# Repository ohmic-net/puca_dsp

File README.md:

# PÚCA DSP

**PÚCA DSP** is an open source, Arduino compatible ESP32 development board for audio and digital signal processing applications. In this repository you will find the hardware design files, and software examples for; 
- Arduino IDE
- VSCode/PlatformIO with Platform Espressif 32 and Framework arduinoespressif32 
- VSCode/PlatformIO with Platform Espressif 32 and Framework espidf
- ESP IDF

# Specifications 

**Processor & Memory**
- Espressif ESP32 Pico D4 Processor
- 32-bit dual core 80MHZ / 160MHZ / 240MHZ
- 4MB SPI Flash with 8MB additional PSRAM or 16MB External SPI Flash 
- Wireless 2.4GHz Wi-Fi -802.11b/g/n
- Bluetooth BLE 4.2
- 3D Antenna

**Audio**
- Wolfson WM8978 Stereo Audio Codec
- Audio Line In on stereo 3.5mm connector
- Audio Headphone / Line Out on stereo 3.5mm connector
- Stereo Aux Line In, Audio Mono Out routed to GPIO Header
- 2 x Knowles SPM0687LR5H-1 MEMS Microphones 
- ESD protection on all audio inputs and outputs
- Support for 8, 11.025, 12, 16, 22.05, 24, 32, 44.1 and 48kHz sample rates
- 1W Speaker Driver, routed to GPIO Header
- DAC SNR 98 dB, THD -84 dB (‘A’ weighted @ 48 kHz)
- ADC SNR 95 dB, THD -84 dB (‘A’ weighted @ 48 kHz)
- Line input impedance: 1 M ohm
- Line output impedance: 33 ohm

**Form Factor and Connectivity**
- Breadboard friendly
- 70mm x 24mm
- 11 x GPIO pins broken out to 2.54mm pitch header, with access to both ESP32 ADC channels, JTAG and capacitive touch pins
- USB 2.0 over USB Type C connector

**Power**
- 3.7/4.2v Lithium Polymer Rechargeable Battery, USB  or external 5V DC power source
- ESP32 and Audio Codec can be placed into low power modes under software control
- Battery voltage level detection
- ESD protection on USB data bus

# Documentation 

# Pin Description

# Absolute Maximum Ratings 

Maximum voltage before clipping on Audio Input, Aux L & Aux R = 3.3V peak-to-peak, AC. Audio input paths are AC coupled. 

Maximum voltage on GPIO pins = 3.3V DC. GPIO pins are not overvoltage protected, for voltages higher than 3.3V use an input protection circuit such as a diode clamp or a level shifter.

# Current Consumption Characteristics 

# Battery Voltage Monitoring
Battery voltage monitoring is available by soldering the BT_LVL solder jumper on the PCB top side, which routes the battery voltage to GPIO 14. 

# Physical Dimensions

*Height measurement is with pin headers soldered. 

# Open Source Licensing 

**PÚCA DSP** is Open Source Hardware Association certified, and can be found on the OSHWA website here; https://certification.oshwa.org/list.html

Hardware design files are released as open source under the CERN v1.2 license. **PÚCA DSP** software examples are released under the MIT license, software examples using Faust DSP also contain additional license information relevant to Faust DSP. Please review these licenses before using these files in your own projects to understand your obligations.

# Video Tutorials
1. Getting started with VS Code and PlatformIO IDE - https://www.youtube.com/watch?v=hKllKXUncVo
2. Configuring the audio codec - https://www.youtube.com/watch?v=Auh9VE7Pjl8

# Need a board?
There are a few available on Tindie - https://www.tindie.com/products/ohmic/puca-dsp/

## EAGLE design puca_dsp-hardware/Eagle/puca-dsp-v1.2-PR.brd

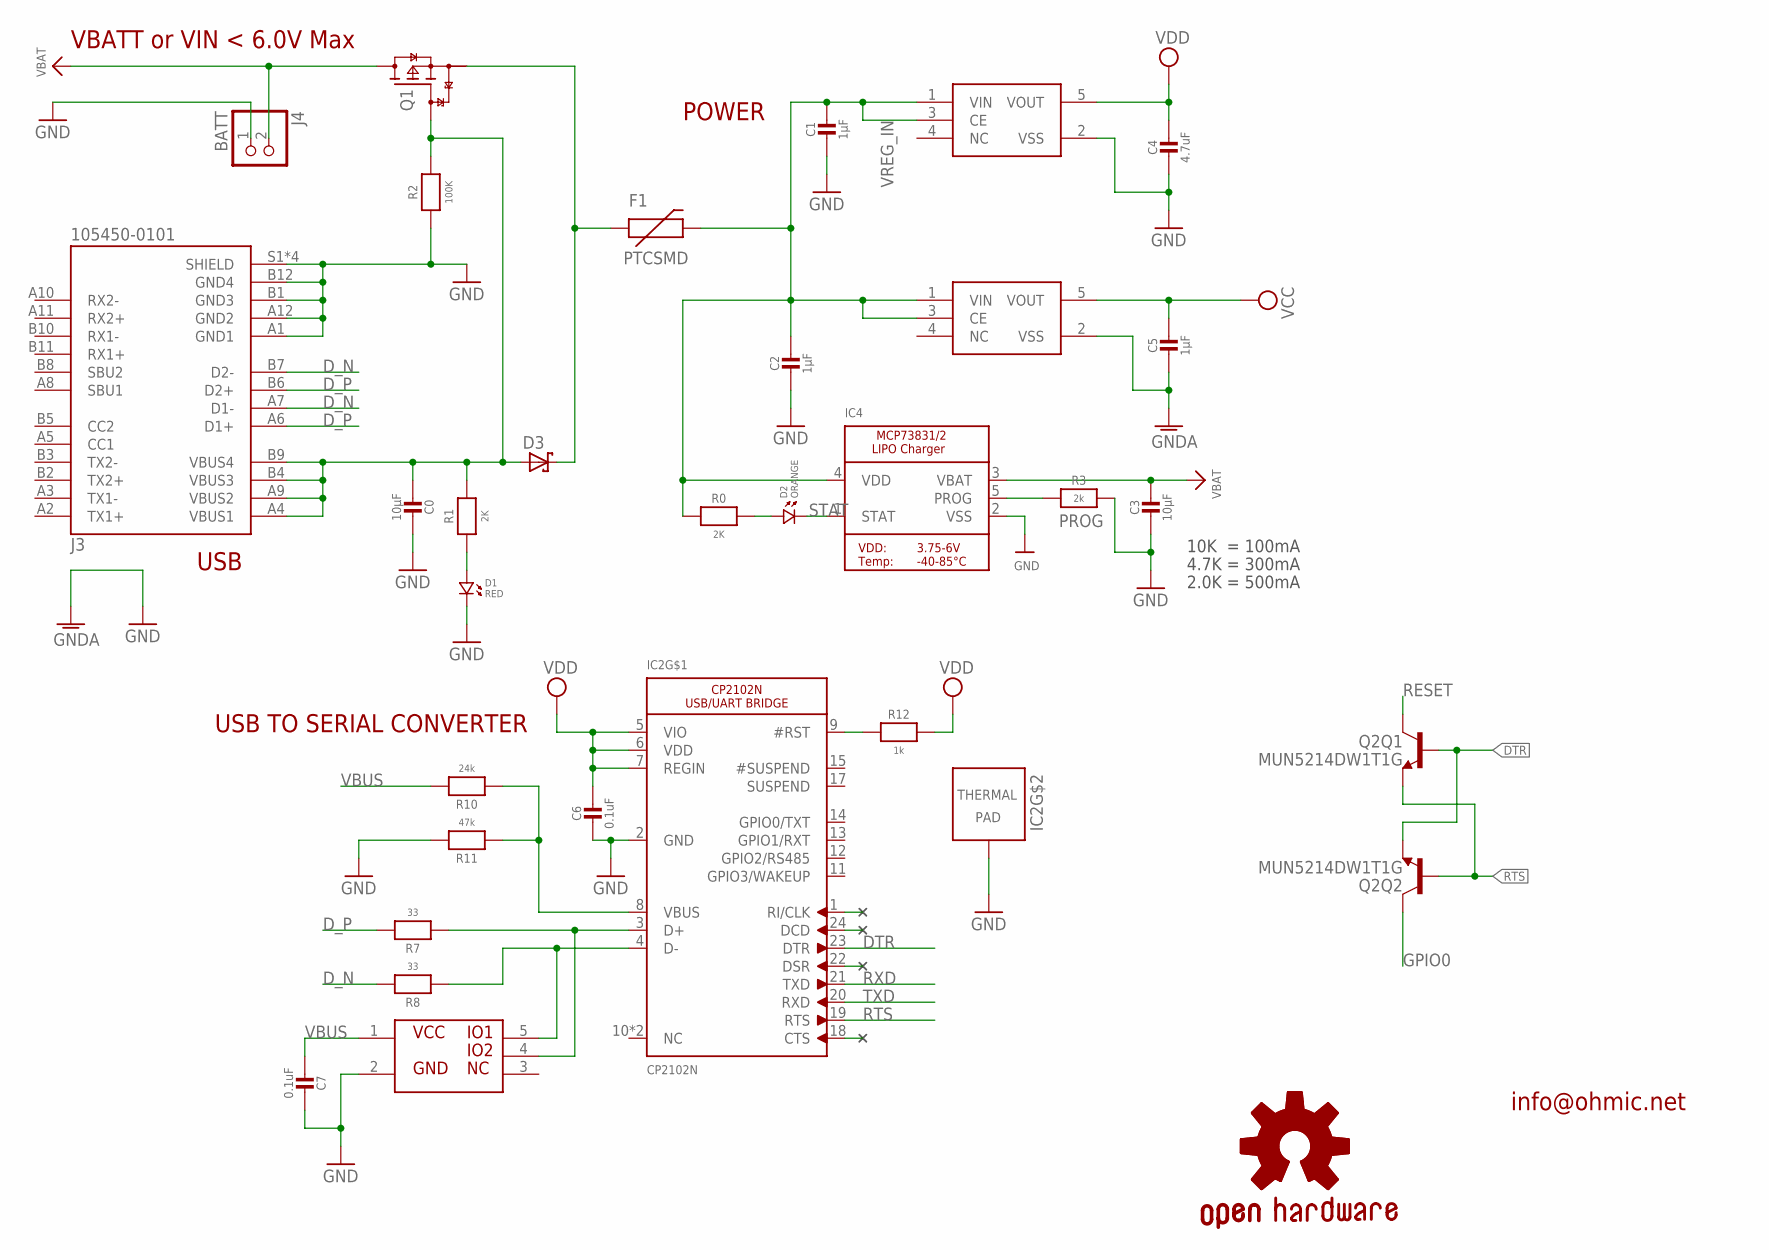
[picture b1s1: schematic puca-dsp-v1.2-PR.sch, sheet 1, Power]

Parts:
C0, C3: 10µF; _0603MP
C1, C2, C5: 1µF; _0402MP
C4: 4.7uF; _0402MP
C6, C7: 0.1uF; _0402MP
D1: RED; 0402.LED
D2: ORANGE; 0402.LED
D3: BAT60J; SOD323_ST
F1: PTCSMD; PTC-1206
GOLD_ORB_SM1: OSHWLOGO_GOLD_ORB_SM; OSHW2
IC2: CP2102N; MICROBUILDER_QFN24_4MM_SMSC
IC4: TP4065-4.2V-SOT25-R; SOT23-5
IC5, IC6: XC6210; SOT95P285X145-5N
IC8: NUP2114UPXV5T1G; SOT50P160X60-5N
J3: 105450-0101; MOLEX_105450-0101
J4: BATT; JST-PH-2-THM
Q1: SSM3J56ACT; SOT883(B)
Q2: MUN5214DW1T1G; DUAL_NPN_SC70-6
R0, R1: 2K; _0402MP
R2: 100K; _0402MP
R3: 2k; _0402MP
R7, R8: 33; _0402MP
R10: 24k; _0402MP
R11: 47k; _0402MP
R12: 1k; _0402MP

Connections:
D1_N: IC2.4 (D-), IC8.5, R8.1
D1_P: IC2.3 (D+), IC8.4, R7.1
DTR: IC2.23 (DTR), Q2.1 (E), Q2.5 (B)
D_N: J3.A7 (D1-), J3.B7 (D2-), R8.2
D_P: J3.A6 (D1+), J3.B6 (D2+), R7.2
GND: C0.1, C1.2, C2.2, C3.2, C4.2, C6.2, C7.1, D1.P$2 (2), IC2.2 (GND), IC2.THERM (TP), IC4.2 (VSS), IC5.2 (VSS), IC8.2, J3.A1 (GND1), J3.A12 (GND2), J3.B1 (GND3), J3.B12 (GND4), J3.S1 (SHIELD), J3.S2 (SHIELD), J3.S3 (SHIELD), J3.S4 (SHIELD), J4.1, R2.2, R3.2, R11.2; also elsewhere on the board
GNDA: C5.2, IC6.2 (VSS); also elsewhere on the board
GPIO0: Q2.6 (C); also elsewhere on the board
unnamed: D1.P$1 (1), R1.1
unnamed: D2.P$1 (1), R0.2
unnamed: IC2.8 (VBUS), R10.1, R11.1
unnamed: D3.C, F1.1, Q1.2 (S)
unnamed: IC2.9 (#RST), R12.1
PROG: IC4.5 (PROG), R3.1
RESET: Q2.3 (C); also elsewhere on the board
RTS: IC2.19 (RTS), Q2.2 (B), Q2.4 (E)
RXD: IC2.21 (TXD); also elsewhere on the board
STAT: D2.P$2 (2), IC4.1 (STAT)
TXD: IC2.20 (RXD); also elsewhere on the board
VBAT: C3.1, IC4.3 (VBAT), J4.2, Q1.3 (D); also elsewhere on the board
VBUS: C0.2, C7.2, D3.A, IC8.1, J3.A4 (VBUS1), J3.A9 (VBUS2), J3.B4 (VBUS3), J3.B9 (VBUS4), Q1.1 (G), R1.2, R2.1, R10.2
VCC: C5.1, IC6.5 (VOUT); also elsewhere on the board
VDD: C4.1, C6.1, IC2.5 (VIO), IC2.6 (VDD), IC2.7 (REGIN), IC5.5 (VOUT), R12.2; also elsewhere on the board
VREG_IN: C1.1, C2.1, F1.2, IC4.4 (VDD), IC5.1 (VIN), IC5.3 (CE), IC6.1 (VIN), IC6.3 (CE), R0.1

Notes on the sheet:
USB TO SERIAL CONVERTER
10K = 100mA
4.7K = 300mA
2.0K = 500mA
VBATT or VIN < 6.0V Max
POWER
info@ohmic.net
USB

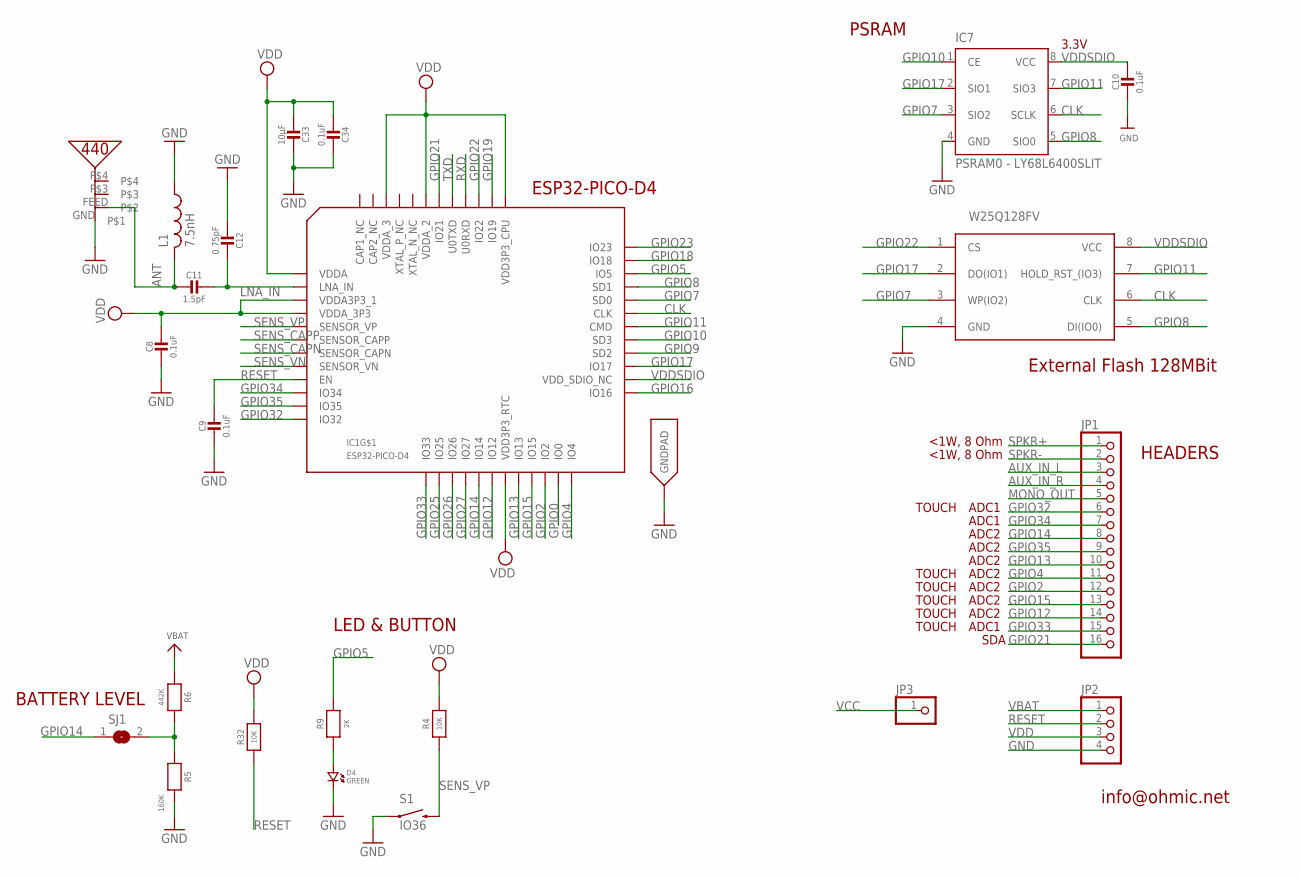
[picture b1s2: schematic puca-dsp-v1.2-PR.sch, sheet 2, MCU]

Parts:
C8, C9, C10, C34: 0.1uF; _0402MP
C11: 1.5pF; _0402MP
C12: 0.75pF; _0402MP
C33: 10µF; _0603MP
D4: GREEN; 0402.LED
IC1: ESP32-PICO-D4; PICO-D4-QFN48
IC7: PSRAM0 - LY68L6400SLIT; SOP8
IC12: PRO-OB-440
JP1: HEADER-1X16ROUND; 1X16_ROUND
JP2: HEADER-1X4ROUND; 1X04_ROUND
JP3: HEADER-1X1ROUND; 1X01_ROUND
L1: 7.5nH; RESC0402_N
R4, R32: 10K; _0402MP
R5: 160K; _0402MP
R6: 442K; _0402MP
R9: 2K; _0402MP
S1: IO36; TACTILE_SWITCH_SMD_4.6X2.8MM
SJ1: SOLDERJUMPER; SOLDERJUMPER_ARROW_NOPASTE
U$1: W25Q128FV; SOIC127P790X216-8N

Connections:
ANT: C11.2, IC12.FEED, L1.2
AUX_IN_L: JP1.3; also elsewhere on the board
AUX_IN_R: JP1.4; also elsewhere on the board
CLK: IC1.31 (CLK), IC7.6 (SCLK), U$1.6 (CLK)
GND: C8.2, C9.2, C10.2, C12.2, C33.1, C34.1, D4.P$2 (2), IC1.EXP (GNDPAD), IC7.4 (GND), IC12.GND, JP2.4, L1.1, R5.2, S1.1, S1.2 (1), U$1.4 (GND); also elsewhere on the board
GPIO0: IC1.23 (IO0); also elsewhere on the board
GPIO2: IC1.22 (IO2), JP1.12
GPIO4: IC1.24 (IO4), JP1.11
GPIO5: IC1.34 (IO5), R9.2
GPIO7: IC1.32 (SD0), IC7.3 (SIO2), U$1.3 (WP(IO2))
GPIO8: IC1.33 (SD1), IC7.5 (SIO0), U$1.5 (DI(IO0))
GPIO9: IC1.28 (SD2)
GPIO10: IC1.29 (SD3), IC7.1 (CE)
GPIO11: IC1.30 (CMD), IC7.7 (SIO3), U$1.7 (HOLD_RST_(IO3))
GPIO12: IC1.18 (IO12), JP1.14
GPIO13: IC1.20 (IO13), JP1.10
GPIO14: IC1.17 (IO14), JP1.8, SJ1.1
GPIO15: IC1.21 (IO15), JP1.13
GPIO16: IC1.25 (IO16)
GPIO17: IC1.27 (IO17), IC7.2 (SIO1), U$1.2 (DO(IO1))
GPIO18: IC1.35 (IO18); also elsewhere on the board
GPIO19: IC1.38 (IO19); also elsewhere on the board
GPIO21: IC1.42 (IO21), JP1.16
GPIO22: IC1.39 (IO22), U$1.1 (CS)
GPIO23: IC1.36 (IO23); also elsewhere on the board
GPIO25: IC1.14 (IO25); also elsewhere on the board
GPIO26: IC1.15 (IO26); also elsewhere on the board
GPIO27: IC1.16 (IO27); also elsewhere on the board
GPIO32: IC1.12 (IO32), JP1.6
GPIO33: IC1.13 (IO33), JP1.15
GPIO34: IC1.10 (IO34), JP1.7
GPIO35: IC1.11 (IO35), JP1.9
LNA_IN: C11.1, C12.1, IC1.2 (LNA_IN)
MONO_OUT: JP1.5; also elsewhere on the board
unnamed: R5.1, R6.2, SJ1.2
unnamed: D4.P$1 (1), R9.1
RESET: C9.1, IC1.9 (EN), JP2.2, R32.1; also elsewhere on the board
RXD: IC1.40 (U0RXD); also elsewhere on the board
SENS_CAPN: IC1.7 (SENSOR_CAPN)
SENS_CAPP: IC1.6 (SENSOR_CAPP)
SENS_VN: IC1.8 (SENSOR_VN)
SENS_VP: IC1.5 (SENSOR_VP), R4.1, S1.3 (2), S1.4 (2)
SPKR+: JP1.1; also elsewhere on the board
SPKR-: JP1.2; also elsewhere on the board
TXD: IC1.41 (U0TXD); also elsewhere on the board
VBAT: JP2.1, R6.1; also elsewhere on the board
VCC: JP3.1; also elsewhere on the board
VDD: C8.1, C33.2, C34.2, IC1.1 (VDDA), IC1.3 (VDDA3P3_1), IC1.4 (VDDA_3P3), IC1.19 (VDD3P3_RTC), IC1.37 (VDD3P3_CPU), IC1.43 (VDDA_2), IC1.46 (VDDA_3), JP2.3, R4.2, R32.2; also elsewhere on the board
VDDSDIO: C10.1, IC1.26 (VDD_SDIO_NC), IC7.8 (VCC), U$1.8 (VCC)

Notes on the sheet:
ESP32-PICO-D4
PSRAM
3.3V
External Flash 128MBit
LED & BUTTON
HEADERS
ADC1
<1W, 8 Ohm
ADC2
SDA
TOUCH
info@ohmic.net
BATTERY LEVEL

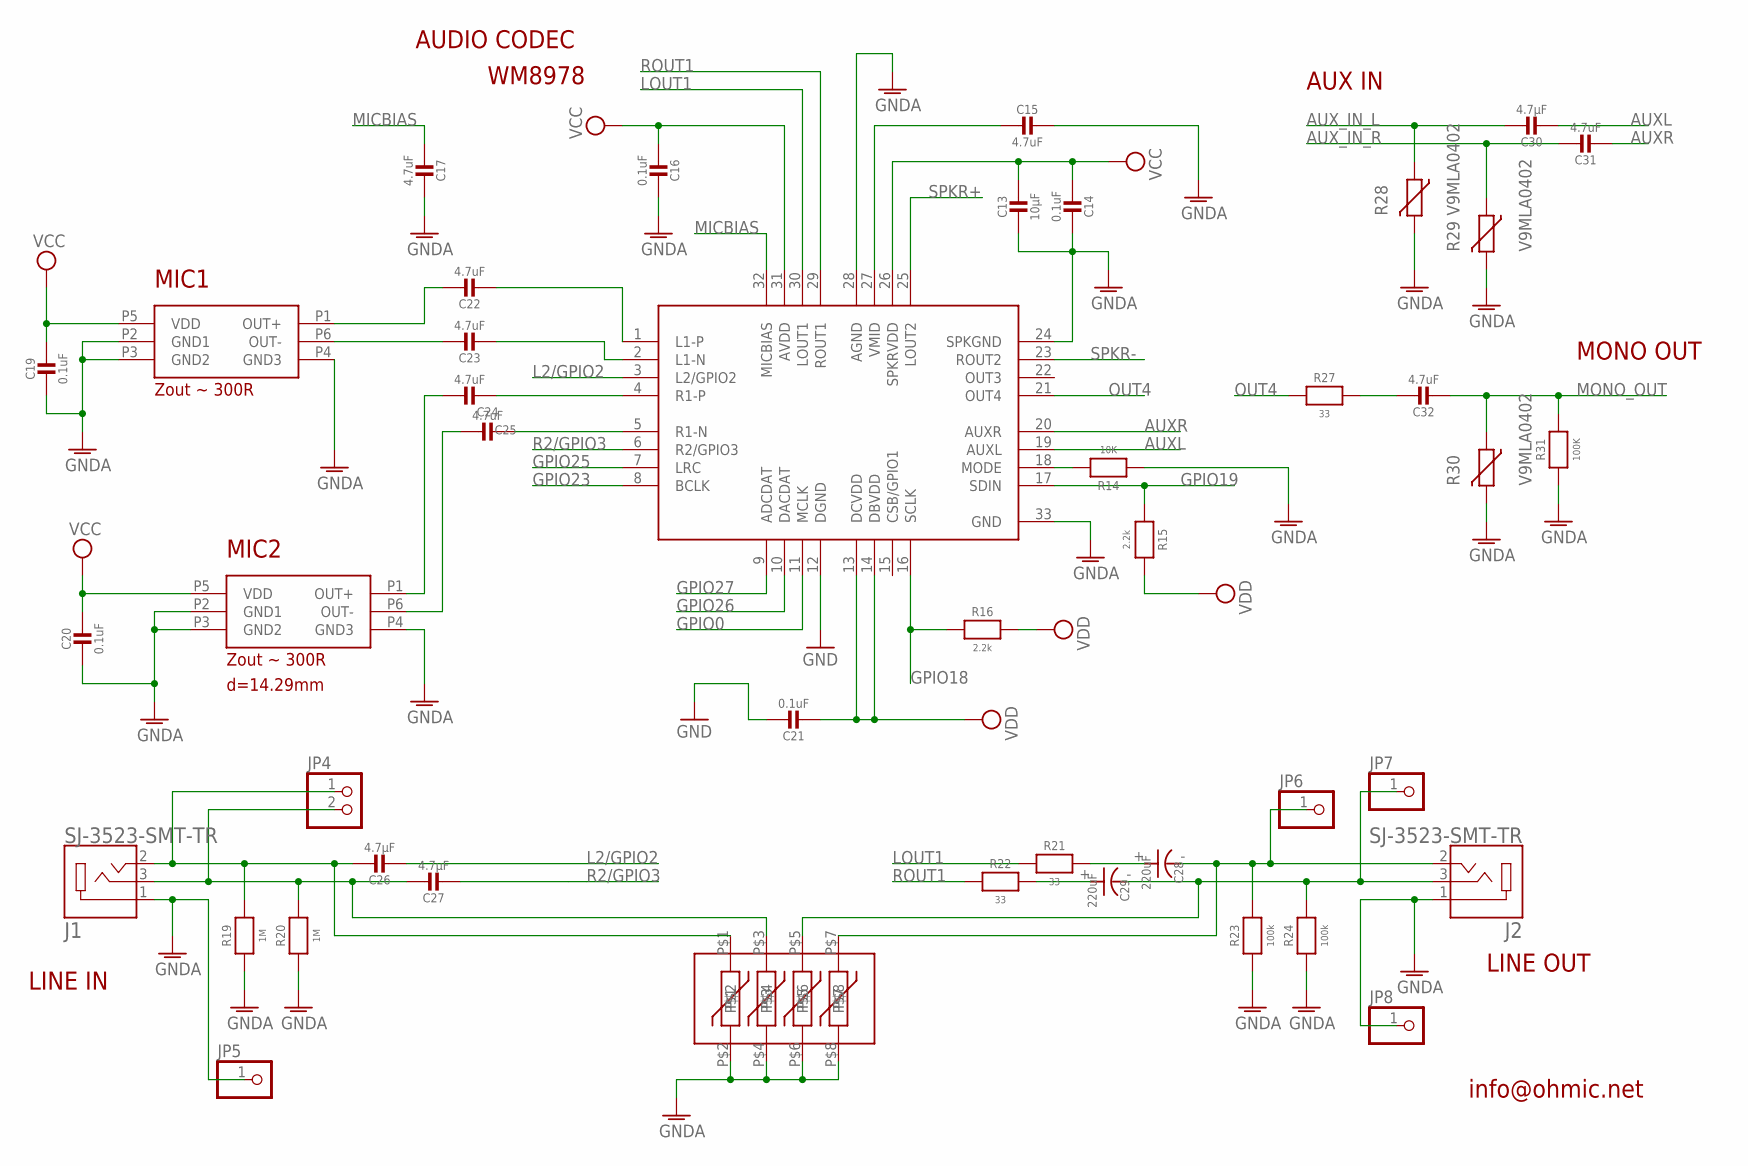
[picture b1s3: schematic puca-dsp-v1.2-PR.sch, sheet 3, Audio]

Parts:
C13: 10µF; _0603MP
C14, C16, C19, C20, C21: 0.1uF; _0402MP
C15, C17: 4.7uF; _0402MP
C22, C23, C24, C25, C31, C32: 4.7uF; _0805MP
C26, C27, C30: 4.7µF; _0805MP
C28, C29: 220uF; 3528
IC3: WM8978; QFN50P500X500X80-33N
IC9, IC10: SPM0687LR5H-1
IC11: V18MLN41206WT
J1, J2: SJ-3523-SMT-TR; CUI_SJ-3523-SMT-TR
JP4: HEADER-1X2ROUND; 1X02_ROUND
JP5, JP6, JP7, JP8: HEADER-1X1ROUND; 1X01_ROUND
R14: 10K; _0402MP
R15, R16: 2.2k; _0402MP
R19, R20: 1M; _0402MP
R21, R22, R27: 33; _0402MP
R23, R24: 100k; _0402MP
R28, R29, R30: V9MLA0402; CT/CN0402
R31: 100K; _0402MP

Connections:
AUXL: C30.2, IC3.19 (AUXL)
AUXR: C31.2, IC3.20 (AUXR)
AUX_IN_L: C30.1, R28.1; also elsewhere on the board
AUX_IN_R: C31.1, R29.1; also elsewhere on the board
GND: C21.1, IC3.12 (DGND); also elsewhere on the board
GNDA: C13.2, C14.1, C15.1, C16.1, C17.1, C19.2, C20.2, IC3.24 (SPKGND), IC3.28 (AGND), IC3.33 (GND), IC9.P2 (GND1), IC9.P3 (GND2), IC9.P4 (GND3), IC10.P2 (GND1), IC10.P3 (GND2), IC10.P4 (GND3), IC11.P$2, IC11.P$4, IC11.P$6, IC11.P$8, J1.1, J2.1, JP5.1, JP8.1, R14.1, R19.1, R20.1, R23.1, R24.1, R28.2, R29.2, R30.2, R31.1; also elsewhere on the board
GPIO0: IC3.11 (MCLK); also elsewhere on the board
GPIO18: IC3.16 (SCLK), R16.1; also elsewhere on the board
GPIO19: IC3.17 (SDIN), R15.1; also elsewhere on the board
GPIO23: IC3.8 (BCLK); also elsewhere on the board
GPIO25: IC3.7 (LRC); also elsewhere on the board
GPIO26: IC3.10 (DACDAT); also elsewhere on the board
GPIO27: IC3.9 (ADCDAT); also elsewhere on the board
L1_N: C23.2, IC3.2 (L1-N)
L1_P: C22.2, IC3.1 (L1-P)
L2/GPIO2: C26.2, IC3.3 (L2/GPIO2)
LINE_IN_L: C26.1, IC11.P$1, J1.2, JP4.1, R19.2
LINE_IN_R: C27.1, IC11.P$3, J1.3, JP4.2, R20.2
LINE_OUT_L: C28.- (1), IC11.P$7, J2.2, JP6.1, R23.2
LINE_OUT_R: C29.- (1), IC11.P$5, J2.3, JP7.1, R24.2
LOUT1: IC3.30 (LOUT1), R21.1
L_N: C23.1, IC9.P6 (OUT-)
L_P: C22.1, IC9.P1 (OUT+)
MICBIAS: C17.2, IC3.32 (MICBIAS)
MONO_OUT: C32.2, R30.1, R31.2; also elsewhere on the board
unnamed: C28.+ (2), R21.2
unnamed: C29.+ (2), R22.2
unnamed: IC3.18 (MODE), R14.2
unnamed: C32.1, R27.2
unnamed: C15.2, IC3.27 (VMID)
OUT4: IC3.21 (OUT4), R27.1
R1_N: C25.2, IC3.5 (R1-N)
R1_P: C24.2, IC3.4 (R1-P)
R2/GPIO3: C27.2, IC3.6 (R2/GPIO3)
ROUT1: IC3.29 (ROUT1), R22.1
R_N: C25.1, IC10.P6 (OUT-)
R_P: C24.1, IC10.P1 (OUT+)
SPKR+: IC3.25 (LOUT2); also elsewhere on the board
SPKR-: IC3.23 (ROUT2); also elsewhere on the board
VCC: C13.1, C14.2, C16.2, C19.1, C20.1, IC3.26 (SPKRVDD), IC3.31 (AVDD), IC9.P5 (VDD), IC10.P5 (VDD); also elsewhere on the board
VDD: C21.2, IC3.13 (DCVDD), IC3.14 (DBVDD), R15.2, R16.2; also elsewhere on the board

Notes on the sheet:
AUDIO CODEC
MIC1
MIC2
Zout ~ 300R
d=14.29mm
WM8978
LINE IN
LINE OUT
AUX IN
MONO OUT
info@ohmic.net

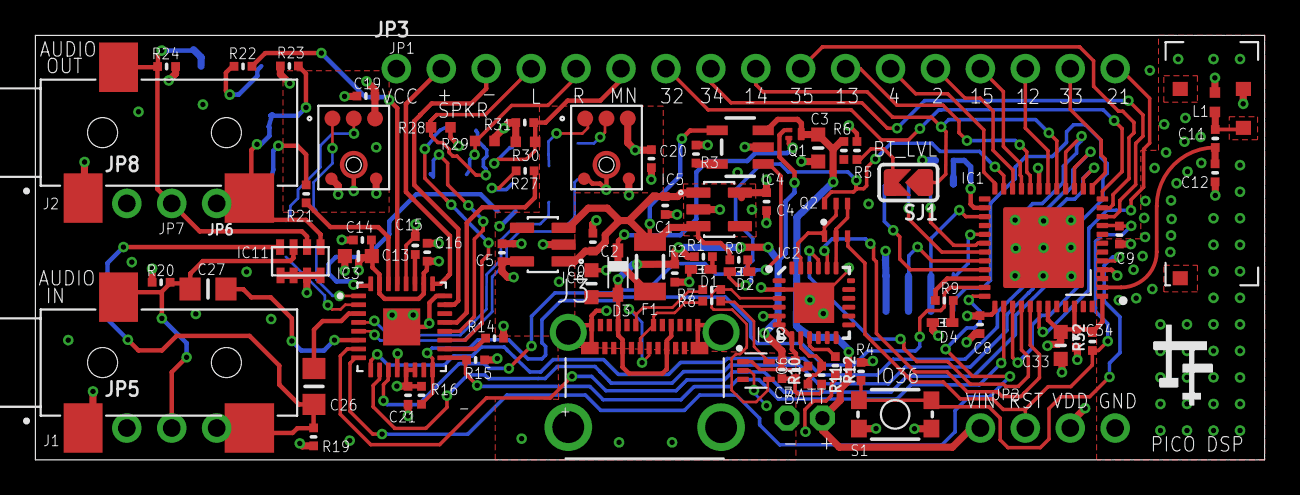
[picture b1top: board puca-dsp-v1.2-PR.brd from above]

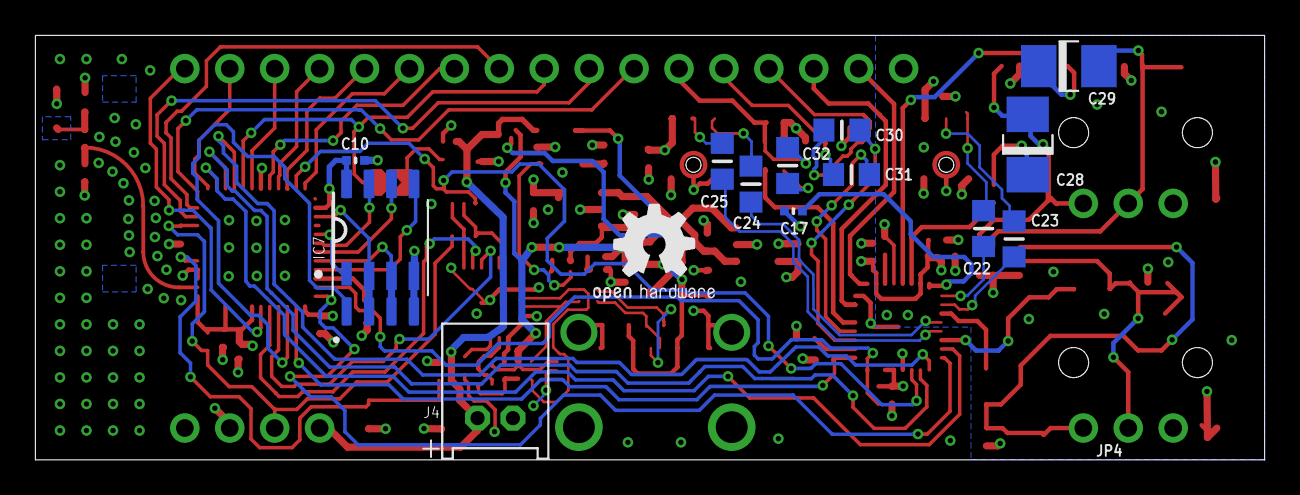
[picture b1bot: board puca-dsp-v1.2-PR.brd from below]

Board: 4 copper layers, 69.5 x 24.0 mm, 98 parts (16 on the bottom side), 85 nets.

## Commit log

2021-08-03 Add Arduino examples
2021-08-03 Create LICENSE
2021-08-03 Move License file
2021-08-03 Add Faust DSP files
2021-08-06 Add v1.0 schematic
2021-08-06 Update v1.0 schematic
2021-08-09 Schematic v1.0 updated
2021-08-10 Add arduino-esp32 examples
2021-08-10 Add mics_omnidirectional
2021-08-10 Add I2S core1 example
2021-08-13 Add mic broadside array example
2021-08-13 Add mics omnidirectional example
2021-08-13 Add i2c clk flag to config
2021-08-17 Add SNES reverb
2021-08-17 Add Faust DSP file
2021-08-19 Add firmware.bin file
2021-08-20 Add endfire array example
2021-08-20 Add passthrough example
2021-08-31 Updates to network.cpp
2021-09-09 Update RTOS tick rate
2021-09-09 Add i2c config clock flag
2021-09-13 Add Arduino as ESP-IDF component example
2022-09-22 Add clock flags, rename folders
2022-11-21 Add OTA example
2022-12-06 Change platform in internet radio example
2022-12-07 Update setup example, add source files
2022-12-07 update setup example
2023-01-03 rename folders, add esp-idf folder
2023-01-03 Add read me for directories
2023-01-04 Add CE certification and datasheet
2023-01-04 Add esp-idf v5 example code
2023-01-04 Update README with build instructions
2023-01-17 Add eurorack hardware tests
2023-02-02 Add stereo mic input example
2023-02-08 Add FFT example
2023-03-10 Add oscillator firmware
2023-03-10 add V/OCT input response graph
2023-03-13 Add binaries
2023-04-05 Add stereo chorus example
2023-04-05 remove data folder
2023-04-13 Update index
2023-04-13 Add OTA update .png file
2023-04-14 Add Eagle files
2023-05-04 update filename
2023-05-11 Define platform
2023-06-02 Update WM8978 library, enable ALC limiter
2023-07-20 Add UKCA Declaration of Conformity
2023-07-20 update declarations of conformity
2023-07-20 update Eurorack binaries
2023-07-26 add codec datasheet
2023-07-31 add video tutorial link
2023-07-31 Add codec setup example
2023-08-29 update codec setup example
2024-03-26 Update schematic pdf file
2024-04-06 Add OSHWA certification
2024-05-17 Add Tindie link
2024-07-31 Add eurorack v0.5 schematic
2024-10-05 Add mono mic input example
2026-02-06 update setup example, new OTA handler
2026-02-07 Update microphone processing example
2026-02-07 update I2S passthrough example
2026-02-07 update Faust example
2026-02-07 update internet radio example
2026-02-08 update fft example
2026-02-08 update chorus example
2026-02-09 remove faust mic example
2026-04-24 Add microphone processing example
2026-04-25 Add karplus strong example

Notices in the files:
parts and their libraries:
microbuilder: This work is placed in the public domain, and may be freely used for commercial and non-commercial work with the following conditions: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
SparkFun-PowerIC: Licensing: Creative Commons ShareAlike 4.0 International - https://creativecommons.org/licenses/by-sa/4.0
